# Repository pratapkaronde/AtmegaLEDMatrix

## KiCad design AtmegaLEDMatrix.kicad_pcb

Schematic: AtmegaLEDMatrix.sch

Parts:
C1, C3: C_Small; C_0402
C2: 0.33u; C_0402
C4: 0.1u; C_0402
C5: 0.1u
D1, D2, D3, D4, D5, D6, D7, D8, D9, D10, D11, D12, D13, D14, D15, D16, D17, D18, D19, D20, D21, D22, D23, D24, D25, D26, D27, D28, D29, D30, D31, D32, D33, D34, D35, D36, D37, D38, D39, D40, D41, D42, D43, D44, D45, D46, D47, D48, D49, D50, D51, D52, D53, D54, D55, D56, D57, D58, D59, D60, D61, D62, D63, D64: LED; LED_0603_HandSoldering
J1: Power; JST_PH_B2B-PH-K_02x2.00mm_Straight
J2: USB_B_Micro; USB_Micro-B
J3: Program; Pin_Header_Straight_2x03_Pitch2.54mm
R1, R2, R3, R4, R5, R6, R7, R8: 330; R_0603_HandSoldering
R9: 10K; R_0603_HandSoldering
SW1: SW_SPST; SW_SPST_B3S-1000
U1: LM7805_TO220; SOT-23
U2: ATmega328-PU; DIP-28_W7.62mm
U3: ULN2802A
Y1: Crystal; Crystal_SMD_0603-2pin_6.0x3.5mm

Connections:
/+5V: C4.1, J3.4, R9.1, U1.3, U2.7 (VCC), U2.20 (AVCC), U2.21 (AREF)
/COL_1: D1.1, D2.1, D3.1, D4.1, D5.1, D6.1, D7.1, D8.1
/COL_2: D9.1, D10.1, D11.1, D12.1, D13.1, D14.1, D15.1, D16.1
/COL_3: D17.1, D18.1, D19.1, D20.1, D21.1, D22.1, D23.1, D24.1
/COL_4: D25.1, D26.1, D27.1, D28.1, D29.1, D30.1, D31.1, D32.1
/COL_5: D33.1, D34.1, D35.1, D36.1, D37.1, D38.1, D39.1, D40.1
/COL_6: D41.1, D42.1, D43.1, D44.1, D45.1, D46.1, D47.1, D48.1
/COL_7: D49.1, D50.1, D51.1, D52.1, D53.1, D54.1, D55.1, D56.1
/COL_8: D57.1, D58.1, D59.1, D60.1, D61.1, D62.1, D63.1, D64.1
/MISO: J3.1, U2.18 (PB4)
/MOSI: J3.5, U2.17 (PB3)
/RESET: J3.3, R9.2, SW1.1, U2.1 (~RESET~/PC6)
/ROW_1: R1.2
/ROW_2: R2.2
/ROW_3: R3.2
/ROW_4: R4.2
/ROW_5: R5.2
/ROW_6: R6.2
/ROW_7: R7.2
/ROW_8: R8.2
/SCK: J3.2, U2.19 (PB5)
/XTAL1: C1.1, U2.9 (XTAL1/PB6), Y1.2
/XTAL2: C3.1, U2.10 (XTAL2/PB7), Y1.1
GND: C1.2, C2.2, C3.2, C4.2, J1.1, J2.5, J2.6, J3.6, SW1.2, U1.2, U2.8 (GND), U2.22 (GND)
unnamed: C2.1, J1.2, U1.1
unnamed: D1.2, D9.2, D17.2, D25.2, D33.2, D41.2, D49.2, D57.2, R1.1
unnamed: D2.2, D10.2, D18.2, D26.2, D34.2, D42.2, D50.2, D58.2, R2.1
unnamed: D3.2, D11.2, D19.2, D27.2, D35.2, D43.2, D51.2, D59.2, R3.1
unnamed: D4.2, D12.2, D20.2, D28.2, D36.2, D44.2, D52.2, D60.2, R4.1
unnamed: D5.2, D13.2, D21.2, D29.2, D37.2, D45.2, D53.2, D61.2, R5.1
unnamed: D6.2, D14.2, D22.2, D30.2, D38.2, D46.2, D54.2, D62.2, R6.1
unnamed: D7.2, D15.2, D23.2, D31.2, D39.2, D47.2, D55.2, D63.2, R7.1
unnamed: D8.2, D16.2, D24.2, D32.2, D40.2, D48.2, D56.2, D64.2, R8.1

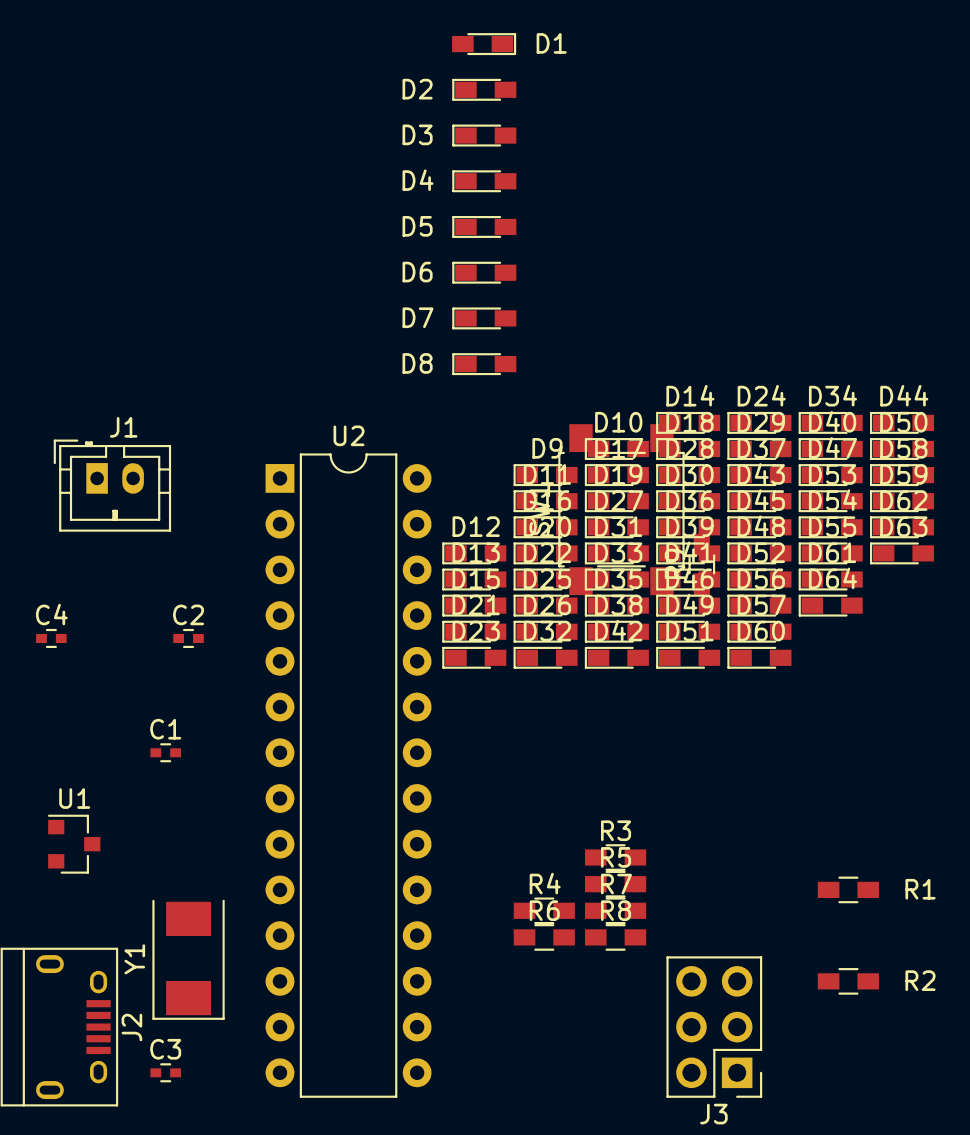
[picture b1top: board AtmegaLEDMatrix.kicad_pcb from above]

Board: 2 copper layers, 84 parts (0 on the bottom side), 25 nets, no tracks yet.

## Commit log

2018-10-27 First commit to local
2018-10-27 Moved a parth
